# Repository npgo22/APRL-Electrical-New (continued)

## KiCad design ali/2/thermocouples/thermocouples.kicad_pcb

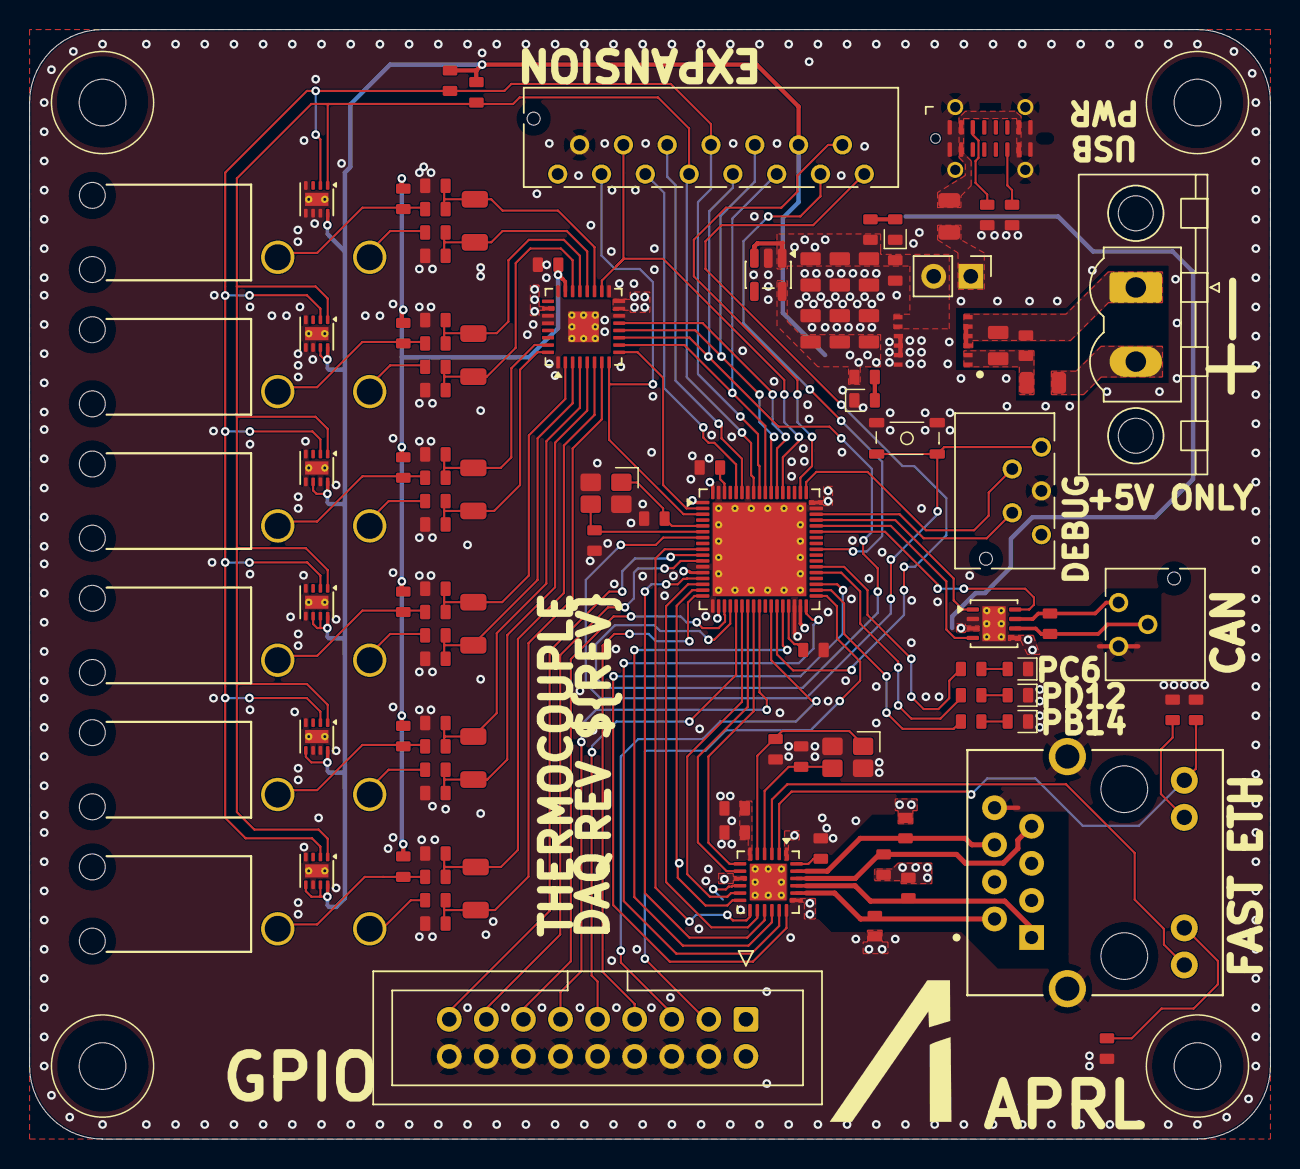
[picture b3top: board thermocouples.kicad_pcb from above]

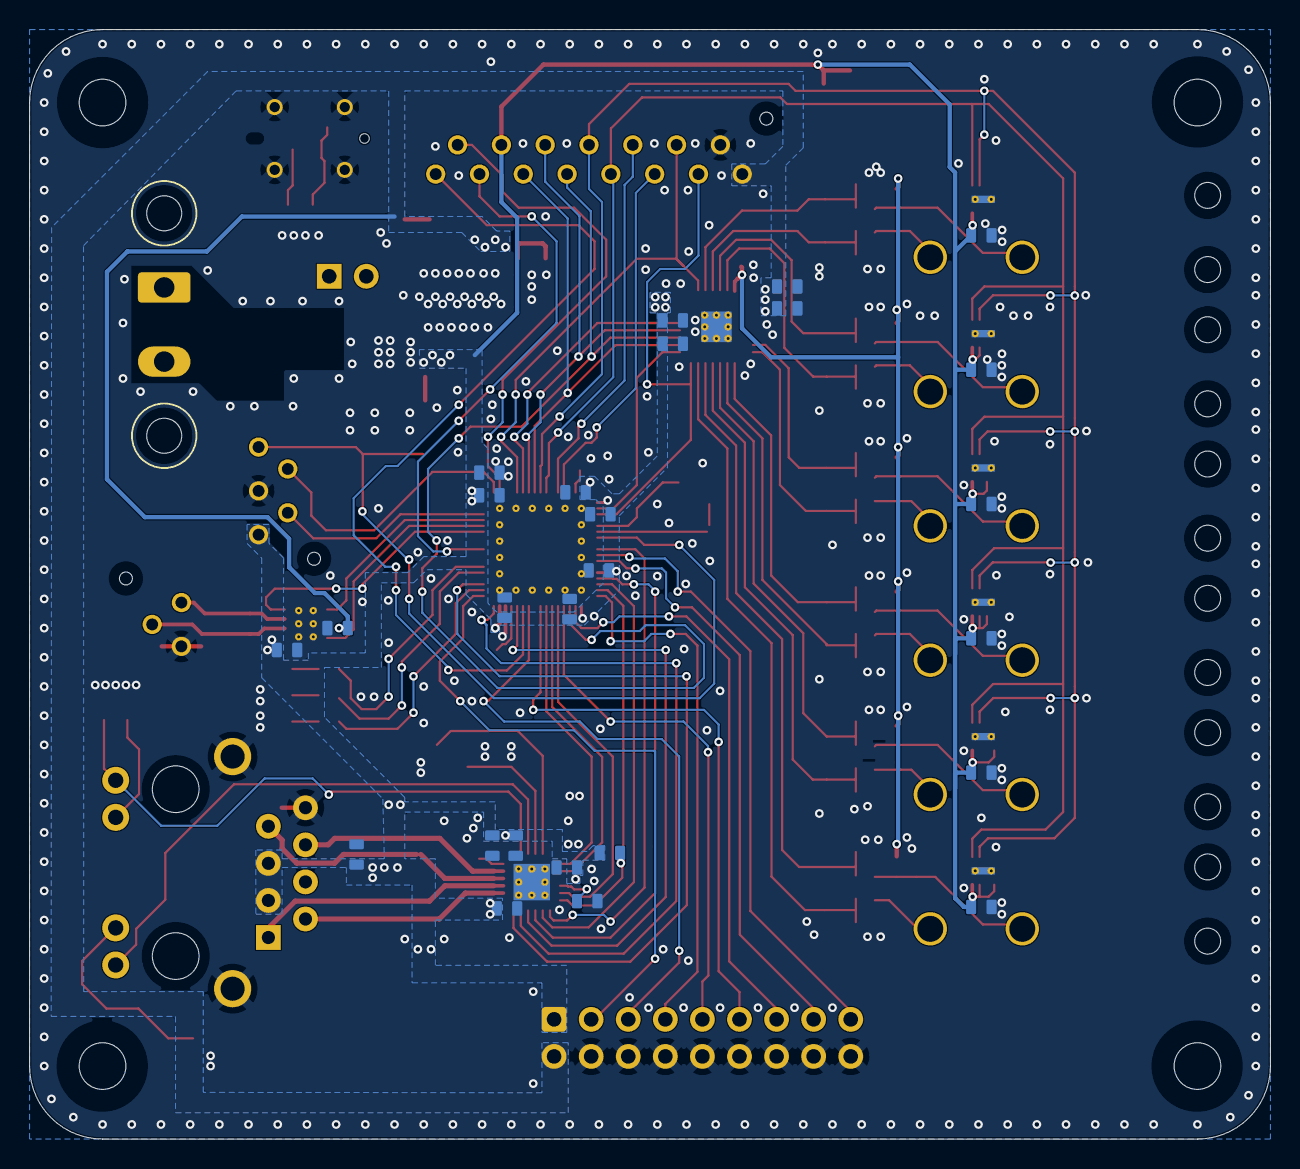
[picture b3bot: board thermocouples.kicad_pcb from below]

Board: 4 copper layers, 85.0 x 76.0 mm, 138 parts (26 on the bottom side), 100 nets.

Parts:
C1, C21, C25, C34, C37, C46: 1uF; C_0603
C2, C3, C4, C5, C6, C7, C22, C23, C24, C29, C31, C35, C36, C55, C56, C57, C58, C59, C60: 100nF; C_0603
C8, C9, C27, C28: 15pF; C_0603
C10, C11: 2.2uF; C_0603
C12, C15, C16, C17, C18, C19, C20: 22uF; C_0805
C13, C14, C32, C33, C40, C41, C42, C43, C47, C48, C49, C50, C53, C54: 10nF; C_0603
C26: 470pF; C_0603
C30: 220nF; C_0603
C38, C39, C44, C45, C51, C52: 100nF; C_1206
D1, D2, D3, D4, D5: LED; LED_0603
F1, F2: 500mA; Fuse_0805_2012Metric
H1, H2, H3, H4: MountingHole; MountingHole_3.2mm_M3
J1: Conn_02x01; PinHeader_1x02_P2.54mm_Vertical
J2: Conn_01x05; Molex_CLIK-Mate_503159-0501_1x05-1MP_P1.50mm_Vertical
J3: USB_C_Receptacle_USB2.0_16P; USB_C_Receptacle_G-Switch_GT-USB-7051x
J4: Conn_01x15; Molex_CLIK-Mate_503159-1501_1x15-1MP_P1.50mm_Vertical
J5: Conn_02x09_Counter_Clockwise; IDC-Header_2x09_P2.54mm_Vertical
J6: Screw_Terminal_01x02; PhoenixContact_MSTBV_2,5_2-GF-5,08_1x02_P5.08mm_Vertical_Th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
J8: Conn_01x03; Molex_CLIK-Mate_503159-0301_1x03-1MP_P1.50mm_Vertical
J9, J10, J11, J12, J13, J14: Conn_01x02; PCC-SMP-V-K
J26: Vertical Ethernet; RJ45_Hanrun_HY951180A_Vertical
R1, R2: 5.1k; R_0603
R3, R4, R5, R6, R7, R17, R51: 10k; R_0603
R11: 120R; R_0603
R12: 1.5k; R_0603
R13, R14, R15, R16: 47R; R_0603
R18: 12.1k; R_0603
R24, R25, R26, R27, R32, R33, R34, R35, R40, R41, R42, R43, R46, R47: 4.7k; R_0603
R28, R29, R30, R31, R36, R37: 10M; R_0603
R52, R53: 330R; R_0603
SW1: SKRPANE010
U1: STM32H563RIV6; QFN-68-1EP_8x8mm_P0.4mm_EP6.4x6.4mm
U2: UCC33420-Q1; VSON-12_4x5mm_P0.65mm
U3: AP2112K-3.3; SOT-23-5
U4: TJA1462ATK; HVSON-8-1EP_3x3mm_P0.65mm_EP1.6x2.4mm_ThermalVias
U5: ADS124S08; Texas_RHB0032M_VQFN-32-1EP_5x5mm_P0.5mm_EP2.1x2.1mm_Thermal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
U7: LAN8742AI; VQFN-24-1EP_4x4mm_P0.5mm_EP2.5x2.5mm_ThermalVias
U14, U17, U18, U19, U20, U21: TMP1075DSG; Texas_DSG0008A_WSON-8-1EP_2x2mm_P0.5mm_EP0.9x1.6mm_ThermalV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
Y1, Y2: 25 MHz; 3225-4P-L

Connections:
+3.3V: C1.1, C2.1, C3.1, C4.1, C5.1, C6.1, C7.1, C18.1, C19.1, C20.1, C21.1, C22.1, C23.1, C24.1, C29.1, C30.1, C34.1, C35.1, C55.1, C56.1, C57.1, C58.1, C59.1, C60.1, J2.1, J4.12, J5.1, J26.3 (TCT), J26.5 (RCT), R4.1, R12.1, R13.1, R14.1, R15.1, R16.1, R46.1, R47.1, U1.1 (VBAT), U1.13 (VDDA), U1.19 (VDD), U1.33 (VDD), U1.51 (VDD), U1.68 (VDD), U3.5 (VOUT), U4.5 (VIO), U5.15 (IOVDD), U5.16 (DVDD), U7.1 (VDD2A), U7.9 (VDDIO), U7.19 (VDD1A), U14.8 (V+), U17.7 (A0), U17.8 (V+), U18.6 (A1), U18.8 (V+), U19.6 (A1), U19.7 (A0), U19.8 (V+), U20.5 (A2), U20.8 (V+), U21.5 (A2), U21.7 (A0), U21.8 (V+)
+5V: C14.2, C15.1, C16.1, C17.1, C31.1, C36.1, C37.1, J1.2, J4.1, J5.2, R3.1, U2.7 (SEL), U2.8 (VCC), U3.1 (VIN), U3.3 (EN), U4.3 (VCC), U5.26 (AVDD)
+ADC_VREF: C46.1, R28.1, R29.1, R30.1, R31.1, R36.1, R37.1, U5.23 (REFOUT)
/ADC/CS: U1.2 (PC13), U5.9 (CS)
/ADC/DRDY: U1.57 (PB3(JTDO), U5.13 (DRDY)
/ADC/MISO: J4.10, U1.58 (PB4(NJTRST)), U5.12 (DOUT/DRDY)
/ADC/MOSI: J4.11, U1.59 (PB5), U5.10 (DIN)
/ADC/RESET: J4.4, U1.56 (PC12), U5.18 (RESET)
/ADC/SCLK: J4.9, U1.21 (PA5), U5.11 (SCLK)
/ADC/START: J4.3, U1.3 (PC14), U5.8 (START/SYNC)
/CJC Sensors/SCL: J4.8, R47.2, U1.60 (PB6), U14.2 (SCL), U17.2 (SCL), U18.2 (SCL), U19.2 (SCL), U20.2 (SCL), U21.2 (SCL)
/CJC Sensors/SDA: J4.7, R46.2, U1.61 (PB7), U14.1 (SDA), U17.1 (SDA), U18.1 (SDA), U19.1 (SDA), U20.1 (SDA), U21.1 (SDA)
/Connectivity/ETH_CRS_DV: U1.23 (PA7), U7.11 (CRS_DV/MODE2)
/Connectivity/ETH_MDC: U1.9 (PC1), U7.13 (MDC)
/Connectivity/ETH_MDIO: R12.2, U1.16 (PA2), U7.12 (MDIO)
/Connectivity/ETH_REF_CLK: U1.15 (PA1), U7.14 (~INT/REFCLKO)
/Connectivity/ETH_RXD0: U1.24 (PC4), U7.8 (RXD0/MODE0)
/Connectivity/ETH_RXD1: U1.25 (PC5), U7.7 (RXD1/MODE1)
/Connectivity/ETH_TXD0: U1.34 (PB12), U7.17 (TXD0)
/Connectivity/ETH_TXD1: U1.37 (PB15), U7.18 (TXD1)
/Connectivity/ETH_TX_EN: U1.30 (PB11), U7.16 (TXEN)
/Connectivity/ETH_~RST: U1.14 (PA0), U7.15 (~RST)
/Connectivity/FDCAN_RX: U1.47 (PA11), U4.4 (RXD)
/Connectivity/FDCAN_STDBY: U1.46 (PA10), U4.8 (STB)
/Connectivity/FDCAN_TX: U1.48 (PA12), U4.1 (TXD)
/Microcontroller/PA4: J5.13, U1.20 (PA4)
/Microcontroller/PA6: J5.9, U1.22 (PA6)
/Microcontroller/PB0: J5.11, U1.26 (PB0)
/Microcontroller/PB2: J5.5, U1.28 (PB2)
/Microcontroller/PB13: J5.3, U1.35 (PB13)
/Microcontroller/PC2: J5.17, U1.10 (PC2)
/Microcontroller/PC3: J5.15, U1.11 (PC3)
/Microcontroller/PC9: J4.13, U1.43 (PC9)
/Microcontroller/SWCLK: J2.4, U1.52 (PA14(JTCK)
/Microcontroller/SWDIO: J2.2, U1.49 (PA13(JTMS)
/Microcontroller/TIM2_CH1: J4.14, U1.53 (PA15(JTDI))
/Microcontroller/TIM2_CH3: J4.15, U1.29 (PB10)
/Microcontroller/TIM2_CH4: J5.7, U1.17 (PA3)
/Microcontroller/UART4_RX: J4.6, U1.63 (PB8)
/Microcontroller/UART4_TX: J4.5, U1.64 (PB9)
/Microcontroller/USER_LED_1: R5.2, U1.36 (PB14)
/Microcontroller/USER_LED_2: R6.2, U1.39 (PD12)
/Microcontroller/USER_LED_3: R7.2, U1.40 (PC6)
/Microcontroller/~RST: J2.5, SW1.3 (K), SW1.4 (A), U1.7 (NRST)
GND: C1.2, C2.2, C3.2, C4.2, C5.2, C6.2, C7.2, C8.2, C9.2, C10.2, C11.2, C14.1, C15.2, C16.2, C17.2, C18.2, C19.2, C20.2, C21.2, C22.2, C23.2, C24.2, C25.2, C26.2, C27.2, C28.2, C29.2, C30.2, C31.2, C32.2, C33.2, C34.2, C35.2, C36.2, C37.2, C40.1, C41.1, C42.2, C43.2, C46.2, C47.1, C48.1, C49.2, C50.2, C53.1, C54.1, C55.2, C56.2, C57.2, C58.2, C59.2, C60.2, D1.1 (K), D2.1 (K), D3.1 (K), D4.1 (K), D5.1 (K), J2.3, J3.A1 (GND), J3.A12 (GND), J3.B1 (GND), J3.B12 (GND), J3.SH (SHIELD), J4.2, J5.4, J5.6, J5.8, J5.10, J5.12, J5.14, J5.16, J5.18, J8.3, J26.8, J26.13, J26.14, R1.1, R2.2, R17.1, R18.2, R51.2, R52.2, R53.2, SW1.1, SW1.2, U1.12 (VSSA), U1.18 (VSS), U1.32 (VSS), U1.50 (VSS), U1.62 (BOOT0), U1.67 (VSS), U1.69 (VSS), U2.9 (GNDS), U2.10 (GNDS), U2.11 (GNDS), U2.12 (GNDS), U3.2 (GND), U4.2 (GND), U4.9 (GND), U5.1 (AINCOM), U5.14 (DGND), U5.17 (CLK), U5.24 (REFCOM), U5.27 (AVSS), U5.28 (AVSS-SW), U5.33 (EP), U7.25 (VSS), U14.4 (GND), U14.5 (A2), U14.6 (A1), U14.7 (A0), U14.9 (EP), U17.4 (GND), U17.5 (A2), U17.6 (A1), U17.9 (EP), U18.4 (GND), U18.5 (A2), U18.7 (A0), U18.9 (EP), U19.4 (GND), U19.5 (A2), U19.9 (EP), U20.4 (GND), U20.6 (A1), U20.7 (A0), U20.9 (EP), U21.4 (GND), U21.6 (A1), U21.9 (EP), Y1.2 (G), Y1.4 (G), Y2.2 (G), Y2.4 (G)
GNDPWR: C12.2, C13.1, J6.1, U2.3 (GNDP), U2.4 (GNDP), U2.5 (GNDP), U2.6 (GNDP)
unnamed: C10.1, U1.31 (VCAP)
unnamed: C11.1, U1.66 (VCAP)
unnamed: D1.2 (A), R5.1
unnamed: D2.2 (A), R3.2
unnamed: D3.2 (A), R4.2
unnamed: D4.2 (A), R6.1
unnamed: D5.2 (A), R7.1
unnamed: F1.1, J3.A4 (VBUS), J3.A9 (VBUS), J3.B4 (VBUS), J3.B9 (VBUS)
unnamed: F1.2, J1.1
unnamed: J3.A5 (CC1), R2.1
unnamed: J3.B5 (CC2), R1.2
unnamed: F2.1, J6.2
unnamed: J8.1, R11.2, U4.7 (CANH)
unnamed: J8.2, R11.1, U4.6 (CANL)
unnamed: J9.1, R24.1
unnamed: J9.2, R26.1, R28.2
unnamed: J10.1, R25.1
unnamed: J10.2, R27.1, R30.2
unnamed: J11.1, R32.1
unnamed: J11.2, R29.2, R34.1
unnamed: J12.1, R33.1
unnamed: J12.2, R31.2, R35.1
unnamed: J13.1, R40.1
unnamed: J13.2, R36.2, R42.1
unnamed: J14.1, R41.1
unnamed: J14.2, R37.2, R43.1
unnamed: J26.10, R52.1
unnamed: J26.11, R53.1
unnamed: J26.6 (RD+), R15.2, U7.23 (RXP)
unnamed: J26.7 (RD-), R16.2, U7.22 (RXN)
unnamed: J26.1 (TD+), R13.2, U7.21 (TXP)
unnamed: J26.2 (TD-), R14.2, U7.20 (TXN)
unnamed: C8.1, U1.5 (PH0), Y1.1
unnamed: C9.1, U1.6 (PH1), Y1.3
unnamed: C12.1, C13.2, F2.2, U2.1 (EN/FLT), U2.2 (VINP)
unnamed: C32.1, C38.2, R24.2, U5.7 (AIN0)
unnamed: C38.1, C40.2, R26.2, U5.6 (AIN1)
unnamed: C33.1, C39.2, R25.2, U5.5 (AIN2)
unnamed: C39.1, C41.2, R27.2, U5.4 (AIN3)
unnamed: C42.1, C44.2, R32.2, U5.3 (AIN4)
unnamed: C44.1, C47.2, R34.2, U5.2 (AIN5)
unnamed: C49.1, C51.2, R40.2, U5.22 (GPIO0/AIN8)
unnamed: C51.1, C53.2, R42.2, U5.21 (GPIO1/AIN9)
unnamed: C50.1, C52.2, R41.2, U5.20 (GPIO2/AIN10)
unnamed: C52.1, C54.2, R43.2, U5.19 (GPIO3/AIN11)
unnamed: C45.1, C48.2, R35.2, U5.31 (REFN1/AIN7)
unnamed: C43.1, C45.2, R33.2, U5.32 (REFP1/AIN6)
unnamed: J26.9, U7.3 (LED1/REGOFF)
unnamed: J26.12, R51.1, U7.2 (LED2/~INTSEL)
unnamed: R18.1, U7.24 (RBIAS)
unnamed: R17.2, U7.10 (RXER/PHYAD0)
unnamed: C25.1, C26.1, U7.6 (VDDCR)
unnamed: C27.1, U7.5 (XTAL1/CLKIN), Y2.1
unnamed: C28.1, U7.4 (XTAL2), Y2.3

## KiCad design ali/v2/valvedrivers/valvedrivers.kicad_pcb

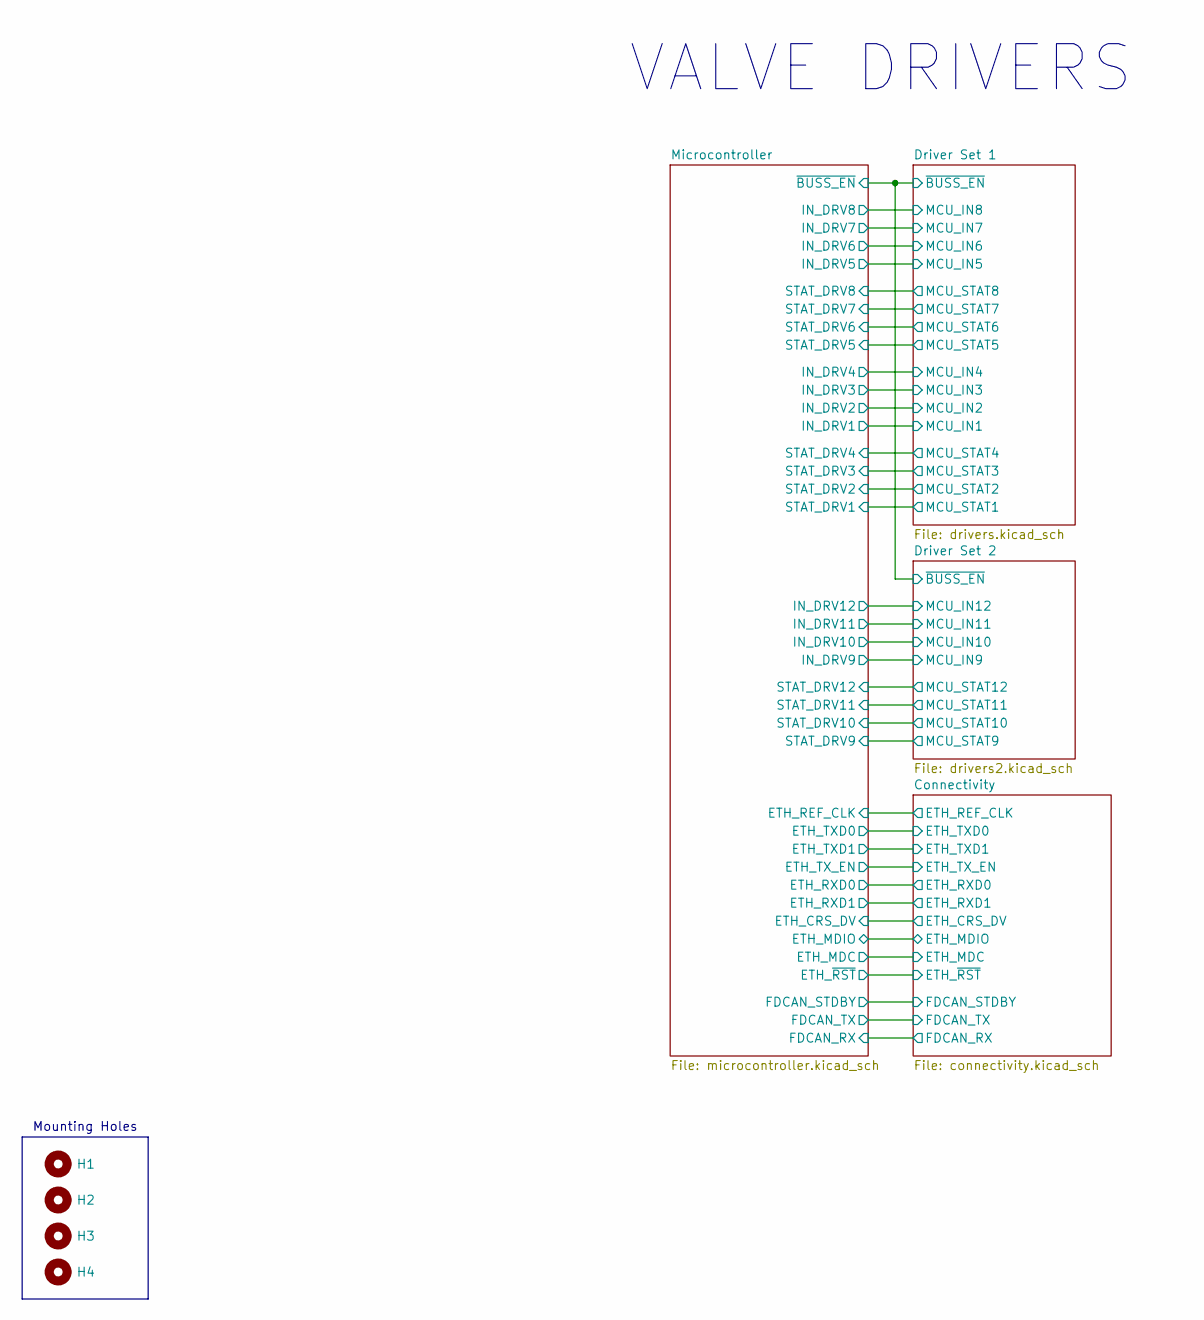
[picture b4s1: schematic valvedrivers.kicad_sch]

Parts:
H1, H2, H3, H4: MountingHole; MountingHole_3.2mm_M3

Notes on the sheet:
VALVE DRIVERS
Mounting Holes

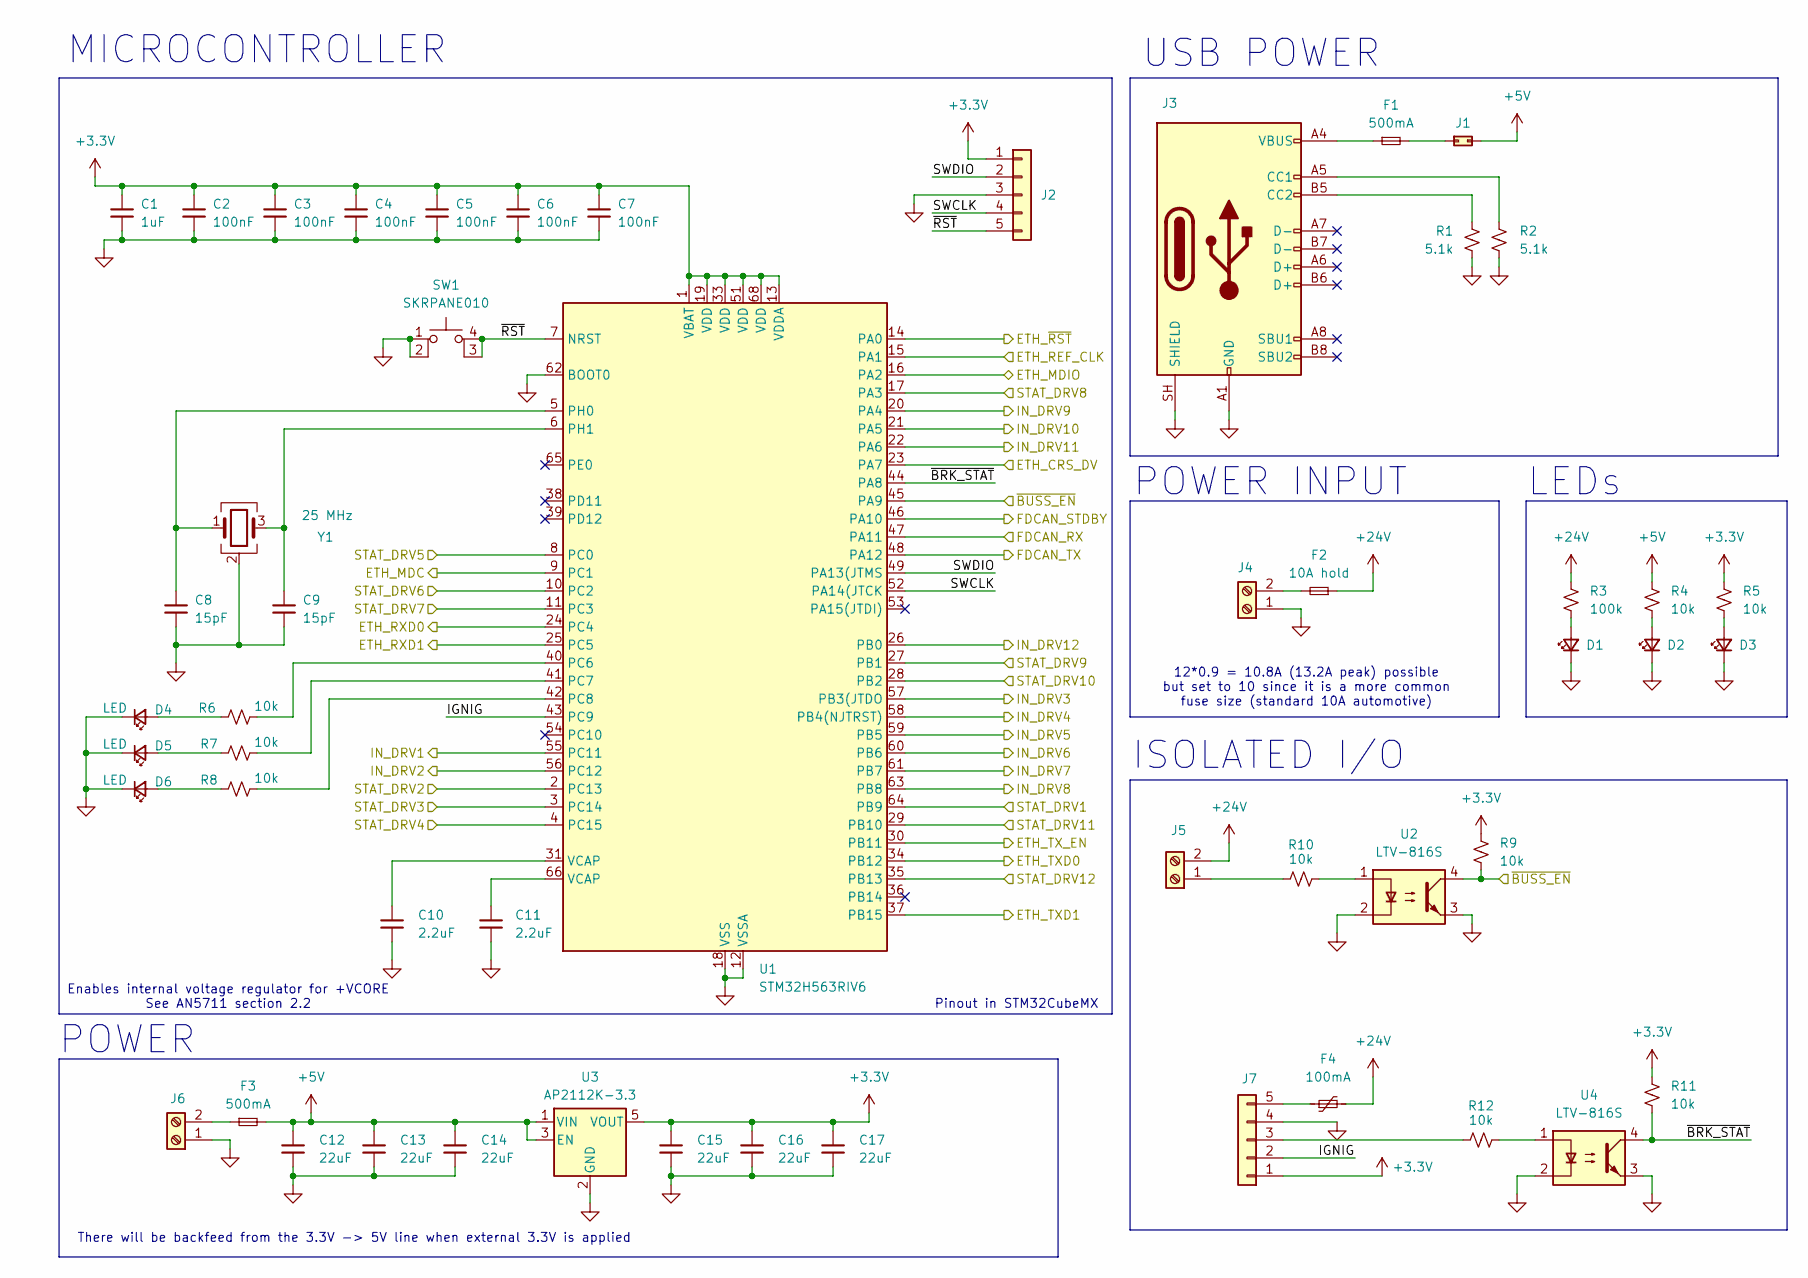
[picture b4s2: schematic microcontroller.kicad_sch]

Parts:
C1: 1uF; C_0603; MPN GRM188D72A105KE01
C2, C3, C4, C5, C6, C7: 100nF; C_0603; MPN GRM188R72A104KA35
C8, C9: 15pF; C_0603; MPN GRM1885C2E150FW07
C10, C11: 2.2uF; C_0603; MPN GRM188R71A225KE15
C12, C13, C14, C15, C16, C17: 22uF; C_0805; MPN GRM21BZ71A226ME15
D1, D2, D3, D4, D5, D6: LED; LED_0603
F1, F3: 500mA; Fuse_0805_2012Metric; MPN 0805L050WR
F2: 10A hold; FuseHolder_Blade_ATO_Littelfuse_FLR_178.6165; MPN 178.6165.0001
F4: 100mA; Fuse_0805_2012Metric; MPN 1206L010/60WR
J1: Conn_02x01; PinHeader_1x02_P2.54mm_Vertical
J2, J7: Conn_01x05; Molex_CLIK-Mate_503159-0501_1x05-1MP_P1.50mm_Vertical; MPN 503159-0501
J3: USB_C_Receptacle_USB2.0_16P; USB_C_Receptacle_G-Switch_GT-USB-7051x; MPN GT-USB-7051A
J4, J5, J6: Screw_Terminal_01x02; PhoenixContact_MSTBV_2,5_2-GF-5,08_1x02_P5.08mm_Vertical_Th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; MPN MSTBV 2,5/ 2-GF-5,08
R1, R2: 5.1k; R_0603; MPN RC0603FR-075K1L
R3: 100k; R_0603; MPN RC0603FR-07100KL
R4, R5, R6, R7, R8, R9, R10, R11, R12: 10k; R_0603; MPN RC0603FR-0710KL
SW1: SKRPANE010; MPN SKRPANE010
U1: STM32H563RIV6; QFN-68-1EP_8x8mm_P0.4mm_EP6.4x6.4mm; MPN STM32H563RIV6
U2, U4: LTV-816S; 4-SMD; MPN LTV-816S-TA1-C
U3: AP2112K-3.3; SOT-23-5; MPN AP2112K-3.3TRG1
Y1: 25 MHz; 3225-4P-L; MPN X1E0000210139

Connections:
+3.3V: C1.1, C2.1, C3.1, C4.1, C5.1, C6.1, C7.1, C15.1, C16.1, C17.1, J2.1, J7.1, R5.1, R9.1, R11.1, U1.1 (VBAT), U1.13 (VDDA), U1.19 (VDD), U1.33 (VDD), U1.51 (VDD), U1.68 (VDD), U3.5 (VOUT); also elsewhere on the board
+5V: C12.1, C13.1, C14.1, F3.2, J1.2, R4.1, U3.1 (VIN), U3.3 (EN); also elsewhere on the board
+24V: F2.1, F4.2, J5.2, R3.1; also elsewhere on the board
/Connectivity/ETH_CRS_DV: U1.23 (PA7); also elsewhere on the board
/Connectivity/ETH_MDC: U1.9 (PC1); also elsewhere on the board
/Connectivity/ETH_MDIO: U1.16 (PA2); also elsewhere on the board
/Connectivity/ETH_REF_CLK: U1.15 (PA1); also elsewhere on the board
/Connectivity/ETH_RXD0: U1.24 (PC4); also elsewhere on the board
/Connectivity/ETH_RXD1: U1.25 (PC5); also elsewhere on the board
/Connectivity/ETH_TXD0: U1.34 (PB12); also elsewhere on the board
/Connectivity/ETH_TXD1: U1.37 (PB15); also elsewhere on the board
/Connectivity/ETH_TX_EN: U1.30 (PB11); also elsewhere on the board
/Connectivity/ETH_~RST: U1.14 (PA0); also elsewhere on the board
/Connectivity/FDCAN_RX: U1.47 (PA11); also elsewhere on the board
/Connectivity/FDCAN_STDBY: U1.46 (PA10); also elsewhere on the board
/Connectivity/FDCAN_TX: U1.48 (PA12); also elsewhere on the board
/Driver Set 1/MCU_IN1: U1.55 (PC11); also elsewhere on the board
/Driver Set 1/MCU_IN2: U1.56 (PC12); also elsewhere on the board
/Driver Set 1/MCU_IN3: U1.57 (PB3(JTDO); also elsewhere on the board
/Driver Set 1/MCU_IN4: U1.58 (PB4(NJTRST)); also elsewhere on the board
/Driver Set 1/MCU_IN5: U1.59 (PB5); also elsewhere on the board
/Driver Set 1/MCU_IN6: U1.60 (PB6); also elsewhere on the board
/Driver Set 1/MCU_IN7: U1.61 (PB7); also elsewhere on the board
/Driver Set 1/MCU_IN8: U1.63 (PB8); also elsewhere on the board
/Driver Set 1/MCU_STAT1: U1.64 (PB9); also elsewhere on the board
/Driver Set 1/MCU_STAT2: U1.2 (PC13); also elsewhere on the board
/Driver Set 1/MCU_STAT3: U1.3 (PC14); also elsewhere on the board
/Driver Set 1/MCU_STAT4: U1.4 (PC15); also elsewhere on the board
/Driver Set 1/MCU_STAT5: U1.8 (PC0); also elsewhere on the board
/Driver Set 1/MCU_STAT6: U1.10 (PC2); also elsewhere on the board
/Driver Set 1/MCU_STAT7: U1.11 (PC3); also elsewhere on the board
/Driver Set 1/MCU_STAT8: U1.17 (PA3); also elsewhere on the board
/Driver Set 1/~BUSS_EN: R9.2, U1.45 (PA9), U2.4; also elsewhere on the board
/Driver Set 2/MCU_IN9: U1.20 (PA4); also elsewhere on the board
/Driver Set 2/MCU_IN10: U1.21 (PA5); also elsewhere on the board
/Driver Set 2/MCU_IN11: U1.22 (PA6); also elsewhere on the board
/Driver Set 2/MCU_IN12: U1.26 (PB0); also elsewhere on the board
/Driver Set 2/MCU_STAT9: U1.27 (PB1); also elsewhere on the board
/Driver Set 2/MCU_STAT10: U1.28 (PB2); also elsewhere on the board
/Driver Set 2/MCU_STAT11: U1.29 (PB10); also elsewhere on the board
/Driver Set 2/MCU_STAT12: U1.35 (PB13); also elsewhere on the board
/Microcontroller/IGNIG: J7.2, U1.43 (PC9)
/Microcontroller/SWCLK: J2.4, U1.52 (PA14(JTCK)
/Microcontroller/SWDIO: J2.2, U1.49 (PA13(JTMS)
/Microcontroller/~BRK_STAT: R11.2, U1.44 (PA8), U4.4
/Microcontroller/~RST: J2.5, SW1.3 (K), SW1.4 (A), U1.7 (NRST)
GND: C1.2, C2.2, C3.2, C4.2, C5.2, C6.2, C7.2, C8.2, C9.2, C10.2, C11.2, C12.2, C13.2, C14.2, C15.2, C16.2, C17.2, D1.1 (K), D2.1 (K), D3.1 (K), D4.1 (K), D5.1 (K), D6.1 (K), J2.3, J3.A1 (GND), J3.A12 (GND), J3.B1 (GND), J3.B12 (GND), J3.SH (SHIELD), J4.1, J6.1, J7.4, R1.1, R2.2, SW1.1, SW1.2, U1.12 (VSSA), U1.18 (VSS), U1.32 (VSS), U1.50 (VSS), U1.62 (BOOT0), U1.67 (VSS), U1.69 (VSS), U2.2, U2.3, U3.2 (GND), U4.2, U4.3, Y1.2 (G), Y1.4 (G); also elsewhere on the board
unnamed: C10.1, U1.31 (VCAP)
unnamed: C11.1, U1.66 (VCAP)
unnamed: D1.2 (A), R3.2
unnamed: D2.2 (A), R4.2
unnamed: D3.2 (A), R5.2
unnamed: D4.2 (A), R6.1
unnamed: D5.2 (A), R7.1
unnamed: D6.2 (A), R8.1
unnamed: F1.1, J3.A4 (VBUS), J3.A9 (VBUS), J3.B4 (VBUS), J3.B9 (VBUS)
unnamed: F1.2, J1.1
unnamed: J3.A5 (CC1), R2.1
unnamed: J3.B5 (CC2), R1.2
unnamed: F2.2, J4.2
unnamed: J5.1, R10.1
unnamed: F3.1, J6.2
unnamed: J7.3, R12.1
unnamed: F4.1, J7.5
unnamed: R10.2, U2.1
unnamed: R12.2, U4.1
unnamed: R6.2, U1.40 (PC6)
unnamed: R7.2, U1.41 (PC7)
unnamed: R8.2, U1.42 (PC8)
unnamed: C8.1, U1.5 (PH0), Y1.1
unnamed: C9.1, U1.6 (PH1), Y1.3

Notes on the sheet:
Enables internal voltage regulator for +VCORE See AN5711 section 2.2
MICROCONTROLLER
There will be backfeed from the 3.3V -> 5V line when external 3.3V is applied
USB POWER
POWER
ISOLATED I/O
Pinout in STM32CubeMX
POWER INPUT
12*0.9 = 10.8A (13.2A peak) possible but set to 10 since it is a more common fuse size (standard 10A automotive)
LEDs

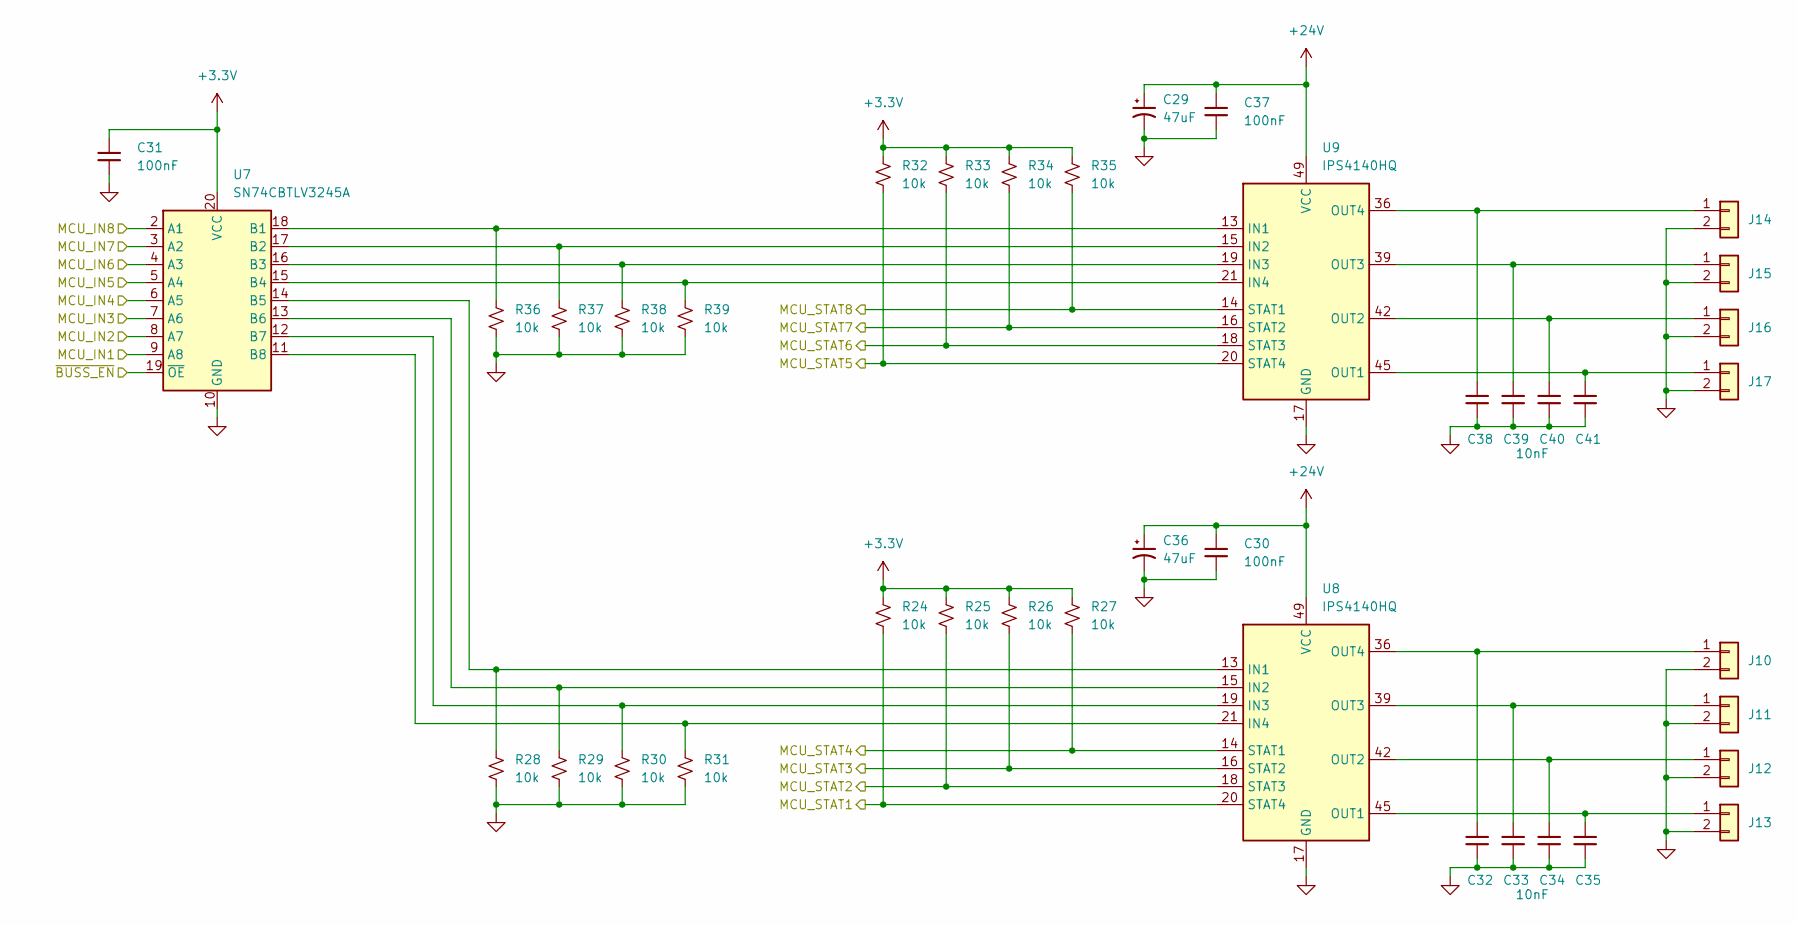
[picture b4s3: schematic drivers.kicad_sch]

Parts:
C29, C36: 47uF; KEMET MU VIB; MPN A767KS476M1JLAE036
C30, C31, C37: 100nF; C_0603; MPN GRM188R72A104KA35
C32, C33, C34, C35, C38, C39, C40, C41: 10nF; C_0603; MPN GRM1885C1H103JA01
J10, J11, J12, J13, J14, J15, J16, J17: Conn_01x02; Molex_CLIK-Mate_503159-0201_1x02-1MP_P1.50mm_Vertical; MPN 503159-0201
R24, R25, R26, R27, R28, R29, R30, R31, R32, R33, R34, R35, R36, R37, R38, R39: 10k; R_0603; MPN AC0603FR-0710KL
U7: SN74CBTLV3245A; TSSOP-20_4.4x6.5mm_P0.65mm; MPN SN74CBTLV3245APWR
U8, U9: IPS4140HQ; QFN-48_EP_9.01x7.01_Pitch0.5mm; MPN IPS4140HQ

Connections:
+3.3V: C31.1, R24.1, R25.1, R26.1, R27.1, R32.1, R33.1, R34.1, R35.1, U7.20 (VCC); also elsewhere on the board
+24V: C29.1, C30.1, C36.1, C37.1, U8.49 (VCC), U9.49 (VCC); also elsewhere on the board
/Driver Set 1/MCU_IN1: U7.9 (A8); also elsewhere on the board
/Driver Set 1/MCU_IN2: U7.8 (A7); also elsewhere on the board
/Driver Set 1/MCU_IN3: U7.7 (A6); also elsewhere on the board
/Driver Set 1/MCU_IN4: U7.6 (A5); also elsewhere on the board
/Driver Set 1/MCU_IN5: U7.5 (A4); also elsewhere on the board
/Driver Set 1/MCU_IN6: U7.4 (A3); also elsewhere on the board
/Driver Set 1/MCU_IN7: U7.3 (A2); also elsewhere on the board
/Driver Set 1/MCU_IN8: U7.2 (A1); also elsewhere on the board
/Driver Set 1/MCU_STAT1: R24.2, U8.20 (STAT4); also elsewhere on the board
/Driver Set 1/MCU_STAT2: R25.2, U8.18 (STAT3); also elsewhere on the board
/Driver Set 1/MCU_STAT3: R26.2, U8.16 (STAT2); also elsewhere on the board
/Driver Set 1/MCU_STAT4: R27.2, U8.14 (STAT1); also elsewhere on the board
/Driver Set 1/MCU_STAT5: R32.2, U9.20 (STAT4); also elsewhere on the board
/Driver Set 1/MCU_STAT6: R33.2, U9.18 (STAT3); also elsewhere on the board
/Driver Set 1/MCU_STAT7: R34.2, U9.16 (STAT2); also elsewhere on the board
/Driver Set 1/MCU_STAT8: R35.2, U9.14 (STAT1); also elsewhere on the board
/Driver Set 1/~BUSS_EN: U7.19 (~OE); also elsewhere on the board
GND: C29.2, C30.2, C31.2, C32.2, C33.2, C34.2, C35.2, C36.2, C37.2, C38.2, C39.2, C40.2, C41.2, J10.2, J11.2, J12.2, J13.2, J14.2, J15.2, J16.2, J17.2, R28.2, R29.2, R30.2, R31.2, R36.2, R37.2, R38.2, R39.2, U7.10 (GND), U8.17 (GND), U9.17 (GND); also elsewhere on the board
unnamed: C32.1, J10.1, U8.36 (OUT4), U8.37 (OUT4), U8.38 (OUT4)
unnamed: C33.1, J11.1, U8.39 (OUT3), U8.40 (OUT3), U8.41 (OUT3)
unnamed: C34.1, J12.1, U8.42 (OUT2), U8.43 (OUT2), U8.44 (OUT2)
unnamed: C35.1, J13.1, U8.45 (OUT1), U8.46 (OUT1), U8.47 (OUT1)
unnamed: C38.1, J14.1, U9.36 (OUT4), U9.37 (OUT4), U9.38 (OUT4)
unnamed: C39.1, J15.1, U9.39 (OUT3), U9.40 (OUT3), U9.41 (OUT3)
unnamed: C40.1, J16.1, U9.42 (OUT2), U9.43 (OUT2), U9.44 (OUT2)
unnamed: C41.1, J17.1, U9.45 (OUT1), U9.46 (OUT1), U9.47 (OUT1)
unnamed: R36.1, U7.18 (B1), U9.13 (IN1)
unnamed: R37.1, U7.17 (B2), U9.15 (IN2)
unnamed: R38.1, U7.16 (B3), U9.19 (IN3)
unnamed: R39.1, U7.15 (B4), U9.21 (IN4)
unnamed: R28.1, U7.14 (B5), U8.13 (IN1)
unnamed: R29.1, U7.13 (B6), U8.15 (IN2)
unnamed: R30.1, U7.12 (B7), U8.19 (IN3)
unnamed: R31.1, U7.11 (B8), U8.21 (IN4)

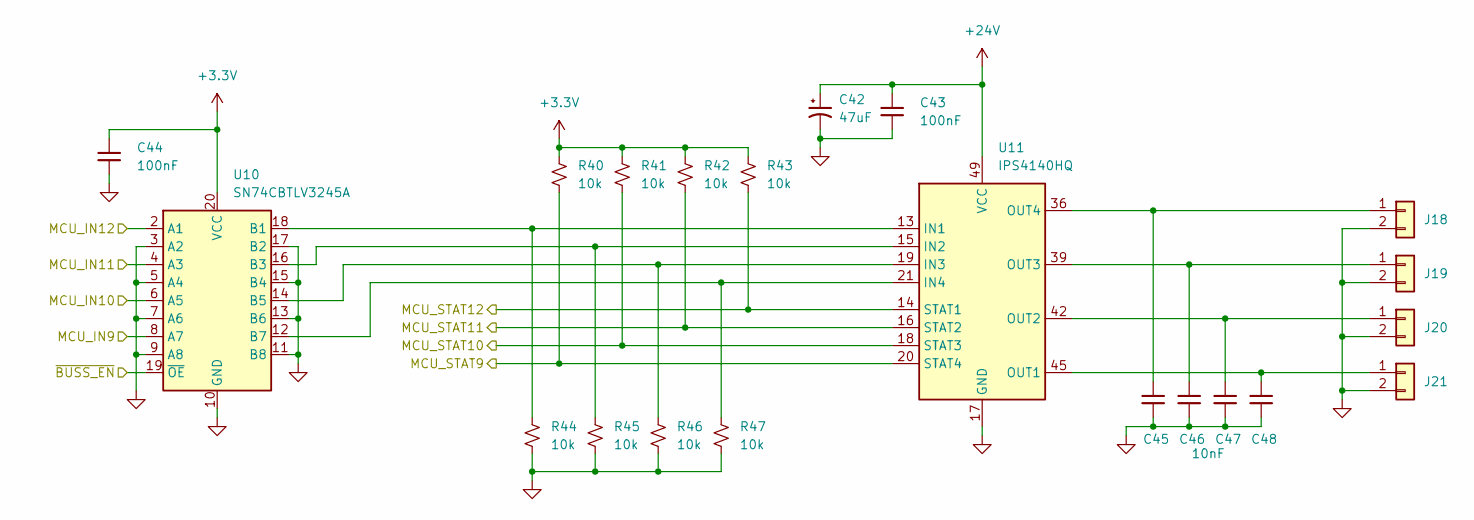
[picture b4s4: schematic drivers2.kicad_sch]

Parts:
C42: 47uF; KEMET MU VIB; MPN A767KS476M1JLAE036
C43, C44: 100nF; C_0603; MPN GRM188R72A104KA35
C45, C46, C47, C48: 10nF; C_0603; MPN GRM1885C1H103JA01
J18, J19, J20, J21: Conn_01x02; Molex_CLIK-Mate_503159-0201_1x02-1MP_P1.50mm_Vertical; MPN 503159-0201
R40, R41, R42, R43, R44, R45, R46, R47: 10k; R_0603; MPN AC0603FR-0710KL
U10: SN74CBTLV3245A; TSSOP-20_4.4x6.5mm_P0.65mm; MPN SN74CBTLV3245APWR
U11: IPS4140HQ; QFN-48_EP_9.01x7.01_Pitch0.5mm; MPN IPS4140HQ

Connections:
+3.3V: C44.1, R40.1, R41.1, R42.1, R43.1, U10.20 (VCC); also elsewhere on the board
+24V: C42.1, C43.1, U11.49 (VCC); also elsewhere on the board
/Driver Set 1/~BUSS_EN: U10.19 (~OE); also elsewhere on the board
/Driver Set 2/MCU_IN9: U10.8 (A7); also elsewhere on the board
/Driver Set 2/MCU_IN10: U10.6 (A5); also elsewhere on the board
/Driver Set 2/MCU_IN11: U10.4 (A3); also elsewhere on the board
/Driver Set 2/MCU_IN12: U10.2 (A1); also elsewhere on the board
/Driver Set 2/MCU_STAT9: R40.2, U11.20 (STAT4); also elsewhere on the board
/Driver Set 2/MCU_STAT10: R41.2, U11.18 (STAT3); also elsewhere on the board
/Driver Set 2/MCU_STAT11: R42.2, U11.16 (STAT2); also elsewhere on the board
/Driver Set 2/MCU_STAT12: R43.2, U11.14 (STAT1); also elsewhere on the board
GND: C42.2, C43.2, C44.2, C45.2, C46.2, C47.2, C48.2, J18.2, J19.2, J20.2, J21.2, R44.2, R45.2, R46.2, R47.2, U10.3 (A2), U10.5 (A4), U10.7 (A6), U10.9 (A8), U10.10 (GND), U10.11 (B8), U10.13 (B6), U10.15 (B4), U10.17 (B2), U11.17 (GND); also elsewhere on the board
unnamed: C45.1, J18.1, U11.36 (OUT4), U11.37 (OUT4), U11.38 (OUT4)
unnamed: C46.1, J19.1, U11.39 (OUT3), U11.40 (OUT3), U11.41 (OUT3)
unnamed: C47.1, J20.1, U11.42 (OUT2), U11.43 (OUT2), U11.44 (OUT2)
unnamed: C48.1, J21.1, U11.45 (OUT1), U11.46 (OUT1), U11.47 (OUT1)
unnamed: R44.1, U10.18 (B1), U11.13 (IN1)
unnamed: R45.1, U10.16 (B3), U11.15 (IN2)
unnamed: R46.1, U10.14 (B5), U11.19 (IN3)
unnamed: R47.1, U10.12 (B7), U11.21 (IN4)
